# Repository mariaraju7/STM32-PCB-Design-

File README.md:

# STM32-PCB-Design-
Created a STM32L476VG development board using Eagle

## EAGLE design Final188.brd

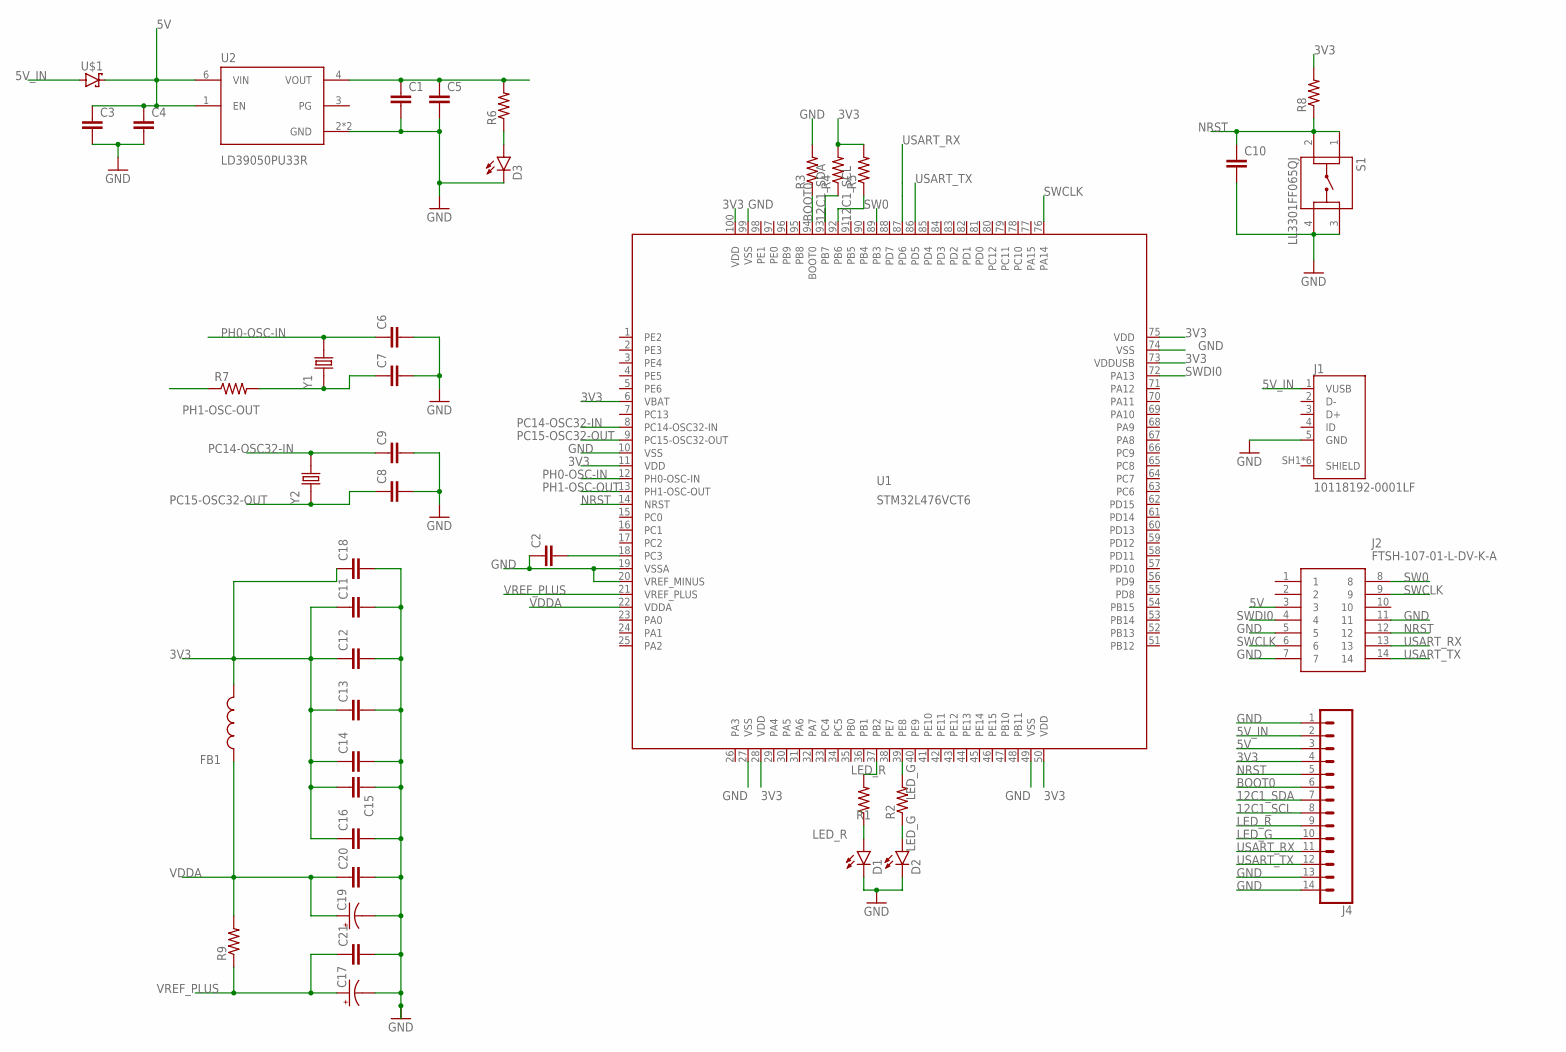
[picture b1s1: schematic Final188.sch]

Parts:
C1, C2, C3: CC0603KRX5R7BB105; CAPC1608X90
C4, C5, C10, C11, C12, C13, C14, C15, C16, C18, C20, C21: CC0402KRX7R7BB104; CAPC1005X55N
C6, C7: CC0402JRNPO9BN200; CAPC1005X55N
C8, C9: CC0402CRNPO9BN4R7; CAPC1005X55N
C17, C19: TAJA105K016RNJ; CAPPM3216X180N
D1, D2: SML-P12MTT86; LED_SML-P11UTT86R
D3: SML-P12VTT86; LED_SML-P11UTT86R
FB1: BK1608HS601-T; BEADC1608X95N
J1: 10118192-0001LF; AMPHENOL_10118192-0001LF
J2: FTSH-107-01-L-DV-K-A; FTSH10701LDVKA
J4: CONN_14; 1X14
R1, R2, R3, R4, R5, R6, R7: RC0402FR-071KL; RESC1005X40N
R8: RC0402FR-0710KL; RESC1005X40N
R9: RT0402FRE07220RL; RESC1005X35N
S1: LL3301FF065QJ
U1: STM32L476VCT6; LQFP100_14X14
U2: LD39050PU33R; SON95P300X300X100-7N
U$1: STPS1L30A; DIOM5226X223N
Y1: ABLS-8.000MHZ-B2-T; XTAL_ABLS-8.000MHZ-B2-T
Y2: ECS-.327-12.5-12QS-TR; XTAL_ECS-.327-12.5-12QS-TR

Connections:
3V3: C11.1, C12.1, C13.1, C14.1, C15.2, C16.1, C18.1, FB1.2, J4.4, R4.2, R5.2, R8.2, U1.6 (VBAT), U1.11 (VDD), U1.28 (VDD), U1.50 (VDD), U1.73 (VDDUSB), U1.75 (VDD), U1.100 (VDD)
5V: C3.1, C4.1, J2.3, J4.3, U2.1 (EN), U2.6 (VIN), U$1.1 (C)
5V_IN: J1.1 (VUSB), J4.2, U$1.2 (A)
12C1_SCL: J4.8, R5.1, U1.92 (PB6)
12C1_SDA: J4.7, R4.1, U1.93 (PB7)
BOOT0: J4.6, R3.1, U1.94 (BOOT0)
GND: C1.2, C2.1, C3.2, C4.2, C5.2, C6.2, C7.2, C8.2, C9.2, C10.2, C11.2, C12.2, C13.2, C14.2, C15.1, C16.2, C17.C (-), C18.2, C19.C (-), C20.2, C21.2, D1.C, D2.C, D3.C, J1.5 (GND), J2.5, J2.7, J2.11, J4.1, J4.13, J4.14, R3.2, S1.3, S1.4, U1.10 (VSS), U1.19 (VSSA), U1.20 (VREF_MINUS), U1.27 (VSS), U1.49 (VSS), U1.74 (VSS), U1.99 (VSS), U2.2 (GND), U2.7 (GND)
LED_G: D2.A, J4.10, R2.1, R2.2, U1.39 (PE8)
LED_R: D1.A, J4.9, R1.1, R1.2, U1.37 (PB2)
unnamed: C2.2, U1.18 (PC3)
unnamed: C1.1, C5.1, R6.2, U2.4 (VOUT)
unnamed: C7.1, R7.2, Y1.1
unnamed: D3.A, R6.1
NRST: C10.1, J2.12, J4.5, R8.1, S1.1, S1.2, U1.14 (NRST)
PC14-OSC32-IN: C9.1, U1.8 (PC14-OSC32-IN), Y2.2
PC15-OSC32-OUT: C8.1, U1.9 (PC15-OSC32-OUT), Y2.1
PH0-OSC-IN: C6.1, U1.12 (PH0-OSC-IN), Y1.2
PH1-OSC-OUT: R7.1, U1.13 (PH1-OSC-OUT)
SW0: J2.8, U1.89 (PB3)
SWCLK: J2.6, J2.9, U1.76 (PA14)
SWDI0: J2.4, U1.72 (PA13)
USART_RX: J2.13, J4.11, U1.87 (PD6)
USART_TX: J2.14, J4.12, U1.86 (PD5)
VDDA: C19.A (+), C20.1, FB1.1, R9.2, U1.22 (VDDA)
VREF_PLUS: C17.A (+), C21.1, R9.1, U1.21 (VREF_PLUS)

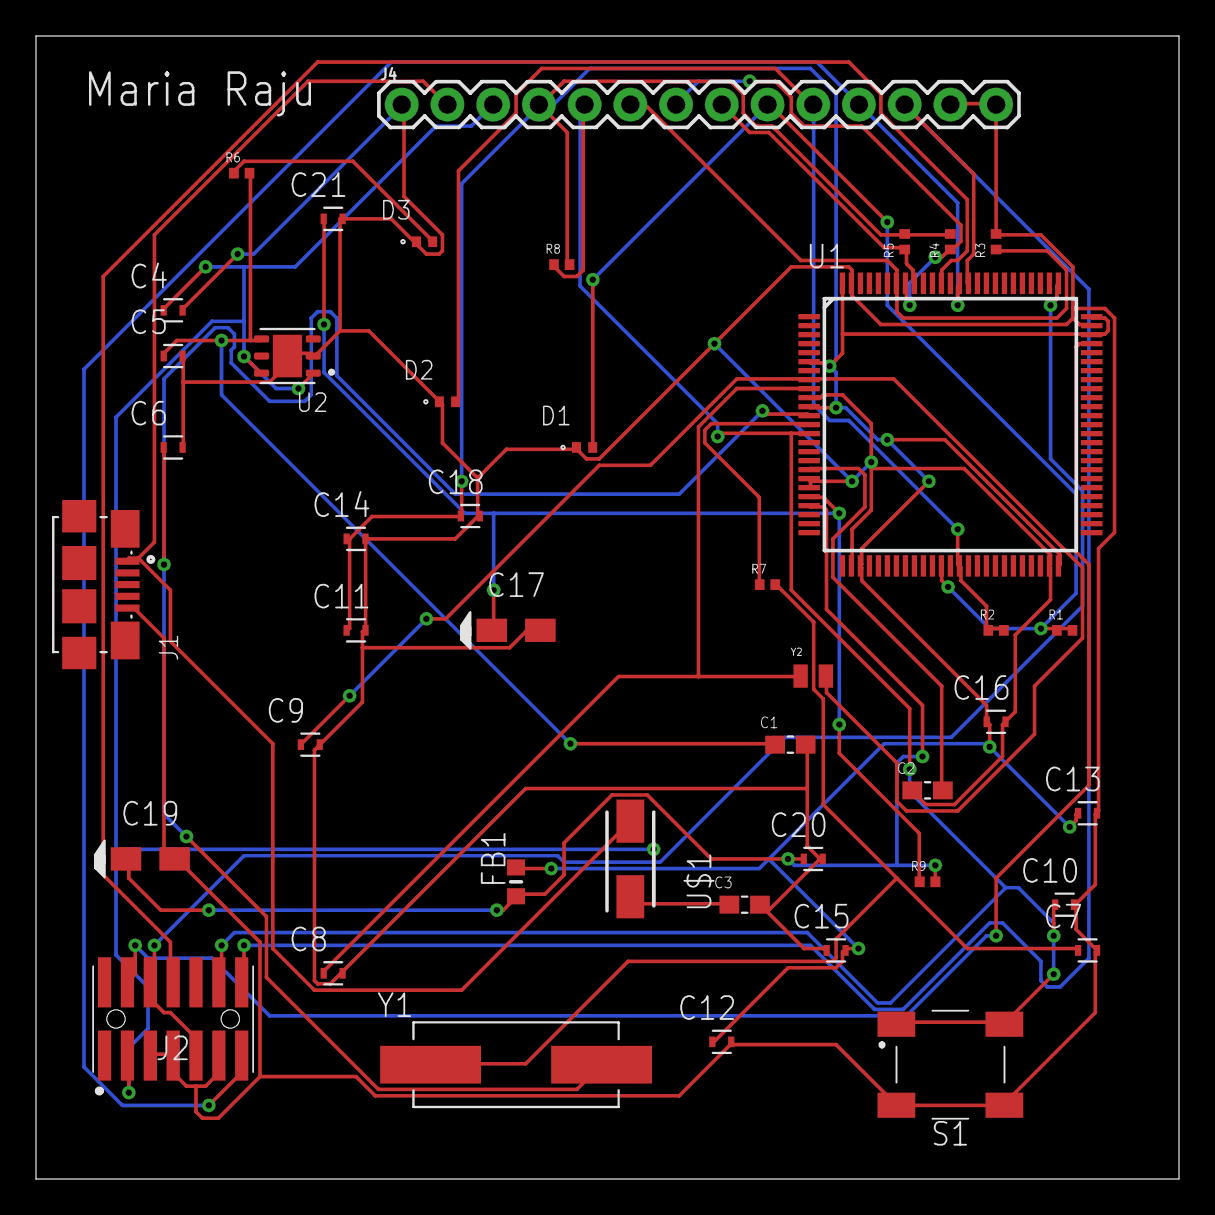
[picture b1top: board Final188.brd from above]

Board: 4 copper layers, 63.5 x 63.5 mm, 43 parts (0 on the bottom side), 25 nets.

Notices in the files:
parts and their libraries:
SparkFun-Connectors: Licensing: Creative Commons ShareAlike 4.0 International - https://creativecommons.org/licenses/by-sa/4.0
